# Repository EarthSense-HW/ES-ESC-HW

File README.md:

# ES-ESC-HW
Hardware source files for EarthSense ESC Based on VESC4

## Modifications from VESC4 Hardware:
* Changed form factor to fit onto EarthSense TerraSentia System Board
* Two IO Pins are broken out for auto-setting CAN ID based on placement on EarthSense TerraSentia System Board
* MOSFETs changed to flat 5x6 packages (STL260N)
* Changed various components in 5v regulator and 3.3v regulator circuits
* Removed IO pins that are not useful to EarthSense TerraSentia Robots
* SWD Programming header broken out to JST-ZH connector
* Two DIO broken out to JST-PH Connector for reading quadrature encoders

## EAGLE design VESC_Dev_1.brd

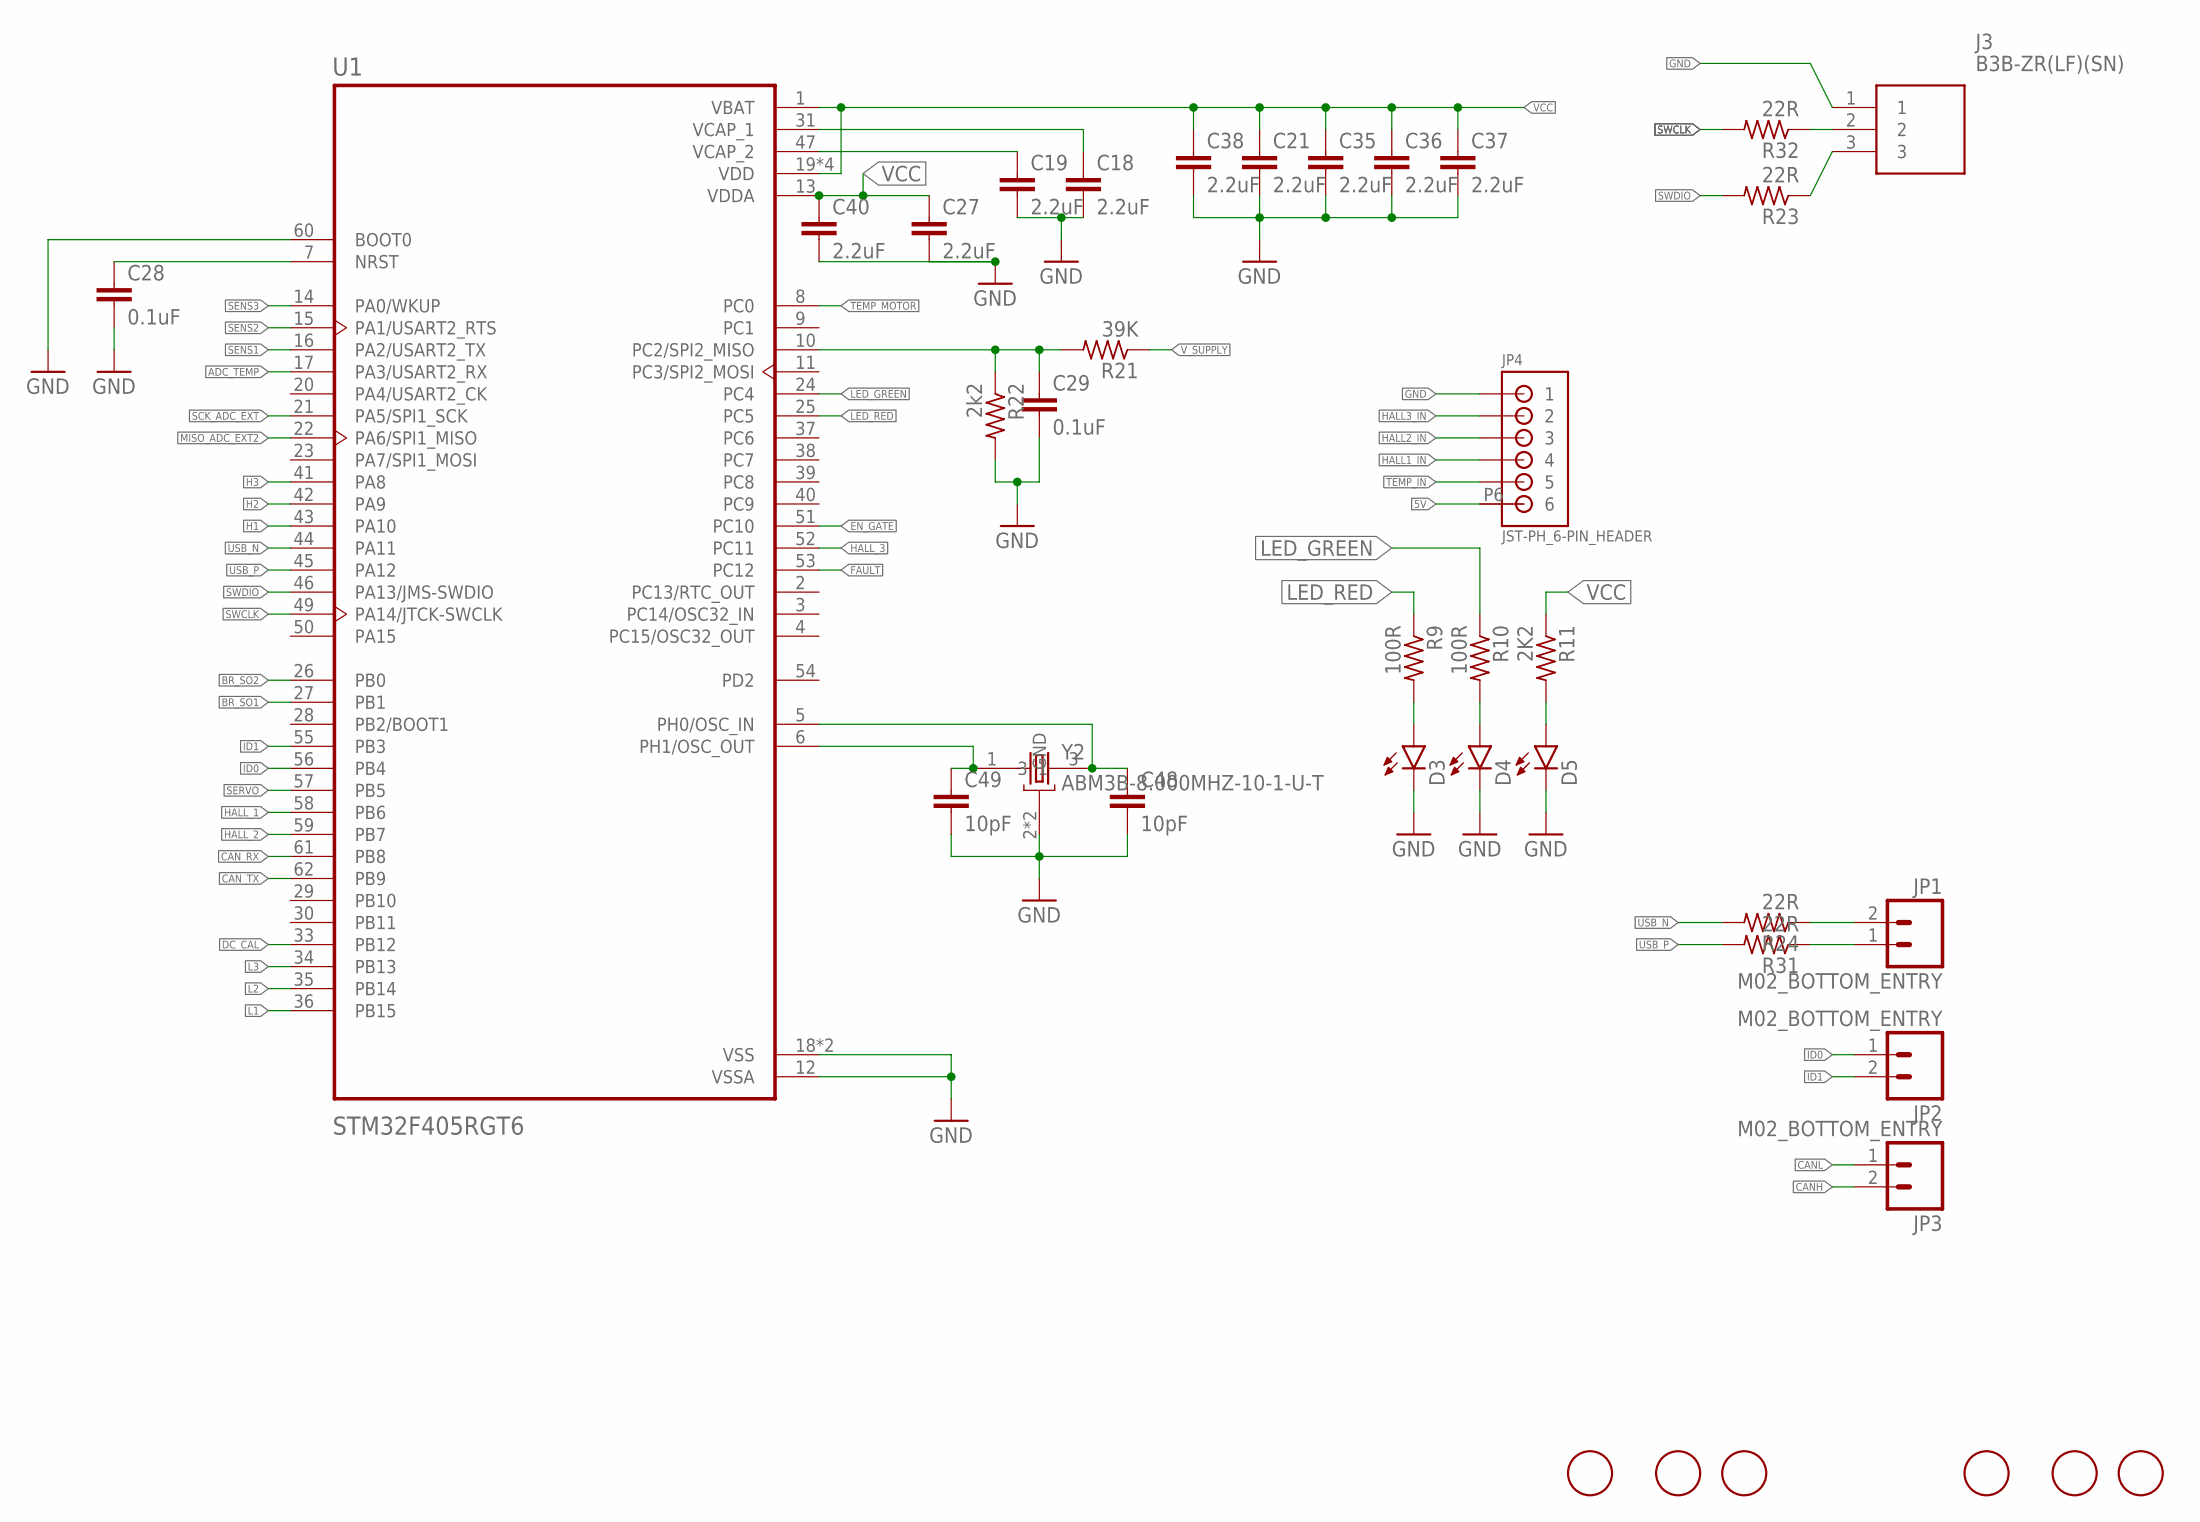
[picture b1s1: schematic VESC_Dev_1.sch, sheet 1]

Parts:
C18, C19, C21, C27, C35, C37, C38, C40: 2.2uF; C0603
C28, C29: 0.1uF; C0603
C36: 2.2uF; C0402
C48, C49: 10pF; C0603
D3, D4, D5: LEDSML0603; SML0603
J3: B3B-ZR(LF)(SN); SHDR3W50P0X150_1X3_600X350X450
JP1, JP2, JP3: M02_BOTTOM_ENTRY; 1X02_BOTTOM_ENTRY
JP4: JST-PH_6-PIN_HEADER; JST_B6B-PH_HEADER
R9, R10: 100R; R0603
R11: 2K2; R0603
R21: 39K; R0603
R22: 2k2; R0603
R23, R24, R31, R32: 22R; R0603
U1: STM32F405RGT6; QFP50P1200X1200X160-64N
U$1, U$2, U$3, U$4, U$5, U$6: FIDUCIAL; FIDUCIAL_1MM
Y2: ABM3B-8.000MHZ-10-1-U-T; OSCCC500X320X110-4N

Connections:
5V: JP4.P6 (6); also elsewhere on the board
ADC_TEMP: U1.17 (PA3/USART2_RX); also elsewhere on the board
BR_SO1: U1.27 (PB1); also elsewhere on the board
BR_SO2: U1.26 (PB0); also elsewhere on the board
CANH: JP3.2; also elsewhere on the board
CANL: JP3.1; also elsewhere on the board
CAN_RX: U1.61 (PB8); also elsewhere on the board
CAN_TX: U1.62 (PB9); also elsewhere on the board
DC_CAL: U1.33 (PB12); also elsewhere on the board
EN_GATE: U1.51 (PC10); also elsewhere on the board
FAULT: U1.53 (PC12); also elsewhere on the board
GND: C18.2, C19.2, C21.2, C27.2, C28.2, C29.2, C35.2, C36.2, C37.2, C38.2, C40.2, C48.2, C49.2, D3.C, D4.C, D5.C, J3.1, JP4.P1 (1), R22.2, U1.12 (VSSA), U1.18 (VSS), U1.60 (BOOT0), U1.63 (VSS), Y2.2 (GND), Y2.4 (GND); also elsewhere on the board
H1: U1.43 (PA10); also elsewhere on the board
H2: U1.42 (PA9); also elsewhere on the board
H3: U1.41 (PA8); also elsewhere on the board
HALL1_IN: JP4.P4 (4); also elsewhere on the board
HALL2_IN: JP4.P3 (3); also elsewhere on the board
HALL3_IN: JP4.P2 (2); also elsewhere on the board
HALL_1: U1.58 (PB6); also elsewhere on the board
HALL_2: U1.59 (PB7); also elsewhere on the board
HALL_3: U1.52 (PC11); also elsewhere on the board
ID0: JP2.1, U1.56 (PB4)
ID1: JP2.2, U1.55 (PB3)
L1: U1.36 (PB15); also elsewhere on the board
L2: U1.35 (PB14); also elsewhere on the board
L3: U1.34 (PB13); also elsewhere on the board
LED_GREEN: R10.1, U1.24 (PC4)
LED_RED: R9.1, U1.25 (PC5)
MISO_ADC_EXT2: U1.22 (PA6/SPI1_MISO)
unnamed: C28.1, U1.7 (NRST)
unnamed: J3.2, R32.1
unnamed: C29.1, R21.2, R22.1, U1.10 (PC2/SPI2_MISO)
unnamed: JP1.2, R24.1
unnamed: C18.1, U1.31 (VCAP_1)
unnamed: JP1.1, R31.1
unnamed: C19.1, U1.47 (VCAP_2)
unnamed: C49.1, U1.6 (PH1/OSC_OUT), Y2.1
unnamed: C48.1, U1.5 (PH0/OSC_IN), Y2.3
unnamed: J3.3, R23.1
unnamed: D3.A, R9.2
unnamed: D4.A, R10.2
unnamed: D5.A, R11.2
SCK_ADC_EXT: U1.21 (PA5/SPI1_SCK)
SENS1: U1.16 (PA2/USART2_TX); also elsewhere on the board
SENS2: U1.15 (PA1/USART2_RTS); also elsewhere on the board
SENS3: U1.14 (PA0/WKUP); also elsewhere on the board
SERVO: U1.57 (PB5)
SWCLK: R32.2, U1.49 (PA14/JTCK-SWCLK)
SWDIO: R23.2, U1.46 (PA13/JMS-SWDIO)
TEMP_IN: JP4.P5 (5)
TEMP_MOTOR: U1.8 (PC0); also elsewhere on the board
USB_N: R24.2, U1.44 (PA11)
USB_P: R31.2, U1.45 (PA12)
VCC: C21.1, C27.1, C35.1, C36.1, C37.1, C38.1, C40.1, R11.1, U1.1 (VBAT), U1.13 (VDDA), U1.19 (VDD), U1.32 (VDD), U1.48 (VDD), U1.64 (VDD); also elsewhere on the board
V_SUPPLY: R21.1; also elsewhere on the board

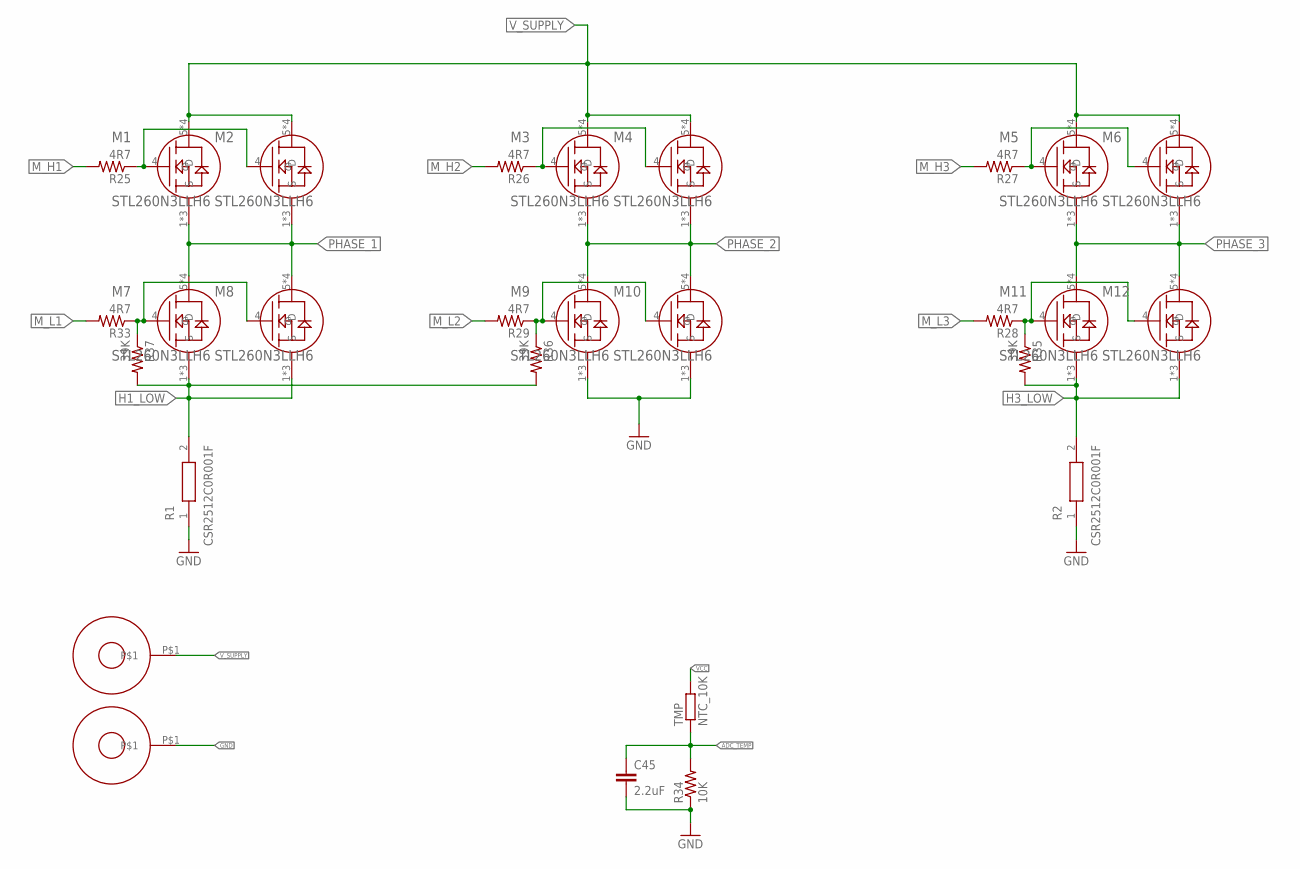
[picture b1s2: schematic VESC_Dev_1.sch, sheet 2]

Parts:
C45: 2.2uF; C0603
M1, M2, M3, M4, M5, M6, M7, M8, M9, M10, M11, M12: STL260N3LLH6; TRANS_STL60P4LLF6
R1, R2: CSR2512C0R001F; RESC6432X85N
R25, R26, R27, R28, R29, R33: 4R7; R0603
R34: 10K; R0603
R35, R36, R37: 39K; R0603
TMP: NTC_10K; R0402
U$7, U$8: M3_POWER_HOLE

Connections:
ADC_TEMP: C45.1, R34.2, TMP.1; also elsewhere on the board
GND: C45.2, M9.1 (S), M9.2 (S), M9.3 (S), M10.1 (S), M10.2 (S), M10.3 (S), R1.1, R2.1, R34.1, U$8.P$1; also elsewhere on the board
H1_LOW: M7.1 (S), M7.2 (S), M7.3 (S), M8.1 (S), M8.2 (S), M8.3 (S), R1.2, R36.2, R37.2; also elsewhere on the board
H3_LOW: M11.1 (S), M11.2 (S), M11.3 (S), M12.1 (S), M12.2 (S), M12.3 (S), R2.2, R35.2; also elsewhere on the board
M_H1: R25.2; also elsewhere on the board
M_H2: R26.2; also elsewhere on the board
M_H3: R27.2; also elsewhere on the board
M_L1: R33.2; also elsewhere on the board
M_L2: R29.2; also elsewhere on the board
M_L3: R28.2; also elsewhere on the board
unnamed: M1.4 (G), M2.4 (G), R25.1
unnamed: M11.4 (G), M12.4 (G), R28.1, R35.1
unnamed: M7.4 (G), M8.4 (G), R33.1, R37.1
unnamed: M3.4 (G), M4.4 (G), R26.1
unnamed: M9.4 (G), M10.4 (G), R29.1, R36.1
unnamed: M5.4 (G), M6.4 (G), R27.1
PHASE_1: M1.1 (S), M1.2 (S), M1.3 (S), M2.1 (S), M2.2 (S), M2.3 (S), M7.5 (D), M7.6 (D), M7.7 (D), M7.8 (D), M8.5 (D), M8.6 (D), M8.7 (D), M8.8 (D); also elsewhere on the board
PHASE_2: M3.1 (S), M3.2 (S), M3.3 (S), M4.1 (S), M4.2 (S), M4.3 (S), M9.5 (D), M9.6 (D), M9.7 (D), M9.8 (D), M10.5 (D), M10.6 (D), M10.7 (D), M10.8 (D); also elsewhere on the board
PHASE_3: M5.1 (S), M5.2 (S), M5.3 (S), M6.1 (S), M6.2 (S), M6.3 (S), M11.5 (D), M11.6 (D), M11.7 (D), M11.8 (D), M12.5 (D), M12.6 (D), M12.7 (D), M12.8 (D); also elsewhere on the board
VCC: TMP.2; also elsewhere on the board
V_SUPPLY: M1.5 (D), M1.6 (D), M1.7 (D), M1.8 (D), M2.5 (D), M2.6 (D), M2.7 (D), M2.8 (D), M3.5 (D), M3.6 (D), M3.7 (D), M3.8 (D), M4.5 (D), M4.6 (D), M4.7 (D), M4.8 (D), M5.5 (D), M5.6 (D), M5.7 (D), M5.8 (D), M6.5 (D), M6.6 (D), M6.7 (D), M6.8 (D), U$7.P$1; also elsewhere on the board

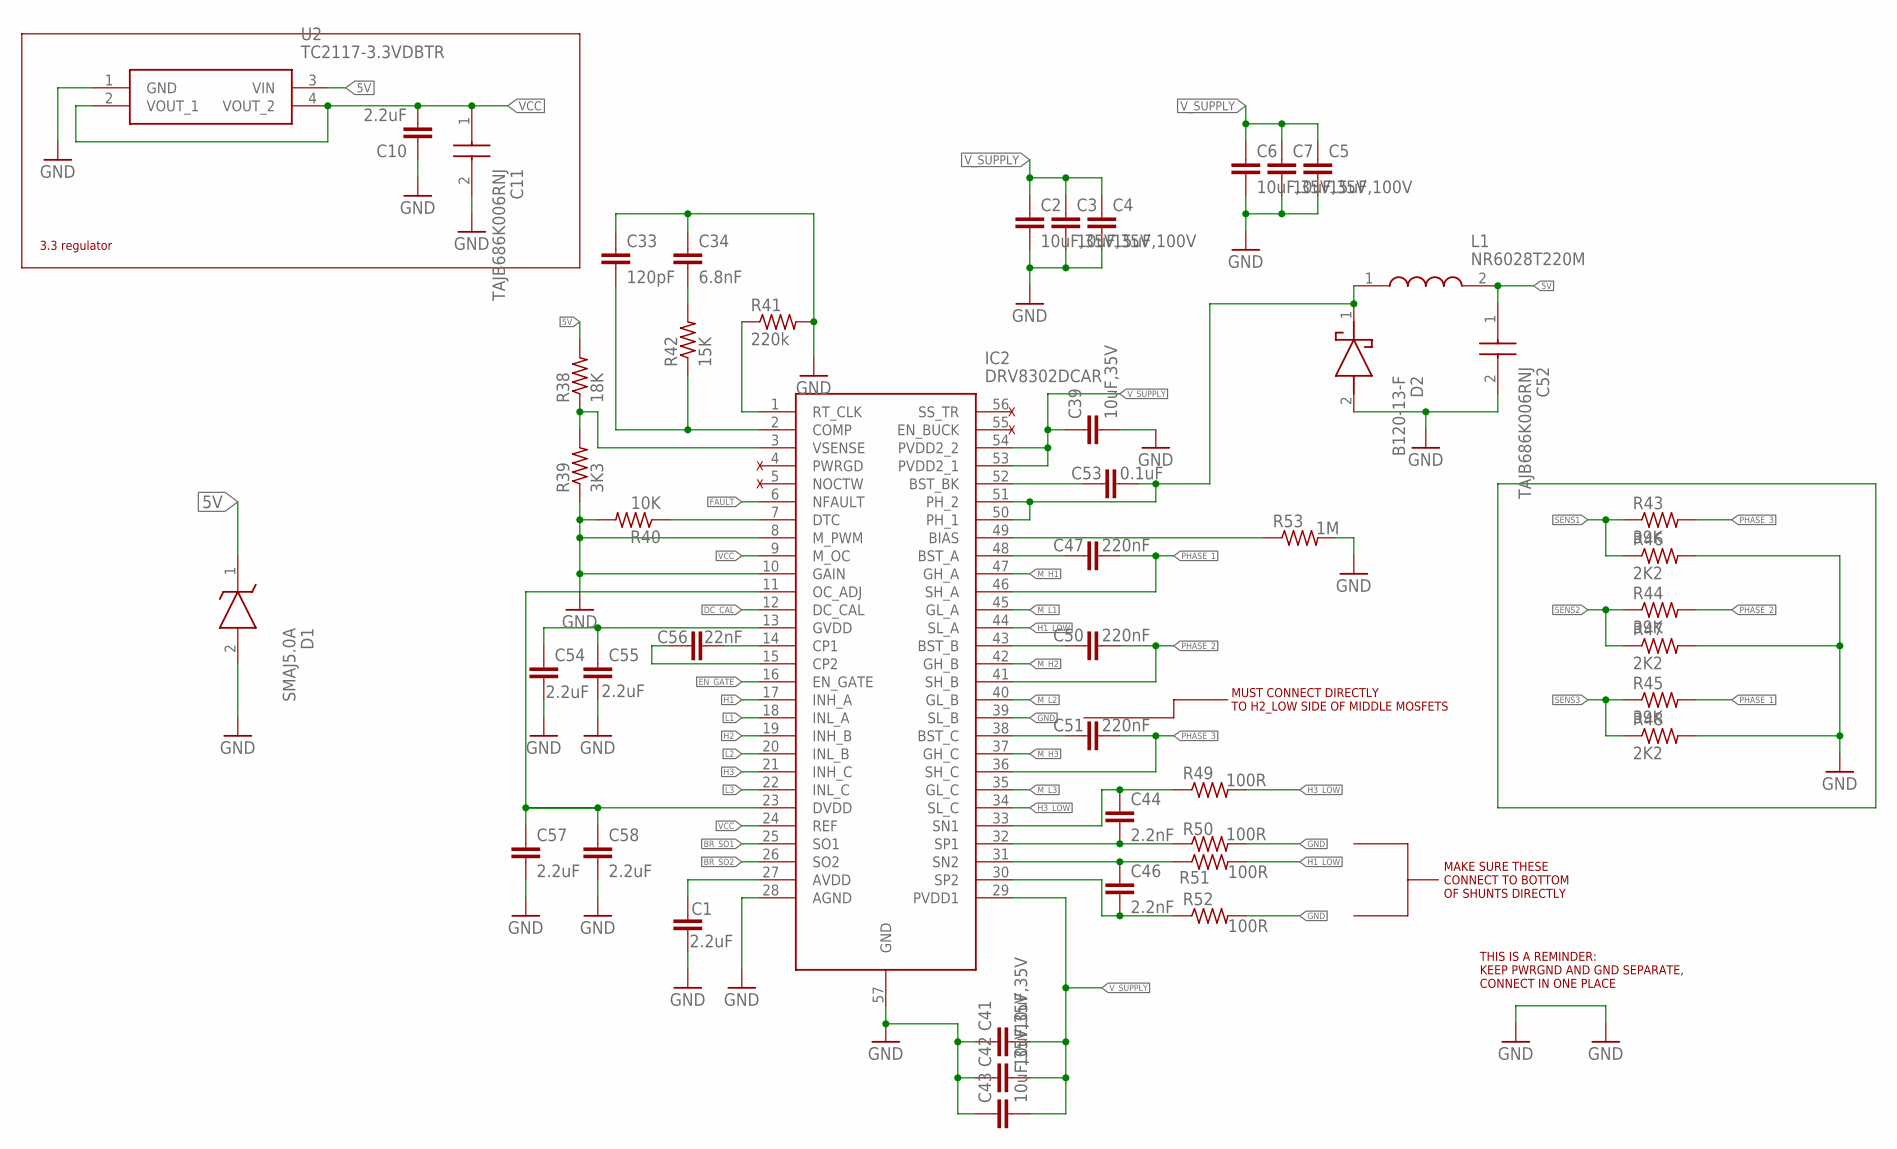
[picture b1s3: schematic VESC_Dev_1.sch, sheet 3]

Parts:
C1, C54, C55: 2.2uF; C0603
C2, C3, C6, C7, C39, C41, C42, C43: 10uF,35V; C0805
C4, C5: 15uF,100V; C2220K
C10: 2.2uF; C0805
C11, C52: TAJB686K006RNJ; CAPPM3528X210N
C33: 120pF; C0402
C34: 6.8nF; C0402
C44, C46: 2.2nF; C0402
C47, C50, C51: 220nF; C0402
C53: 0.1uF; C0603
C56: 22nF; C0402
C57, C58: 2.2uF; C0402
D1: SMAJ5.0A; DIOM5026X229N
D2: B120-13-F; DIOM5226X240N
IC2: DRV8302DCAR; SOP50P810X120-57N
L1: NR6028T220M
R38: 18K; R0402
R39: 3K3; R0402
R40: 10K; R0603
R41: 220k; R0402
R42: 15K; R0402
R43, R44, R45: 39K; R0603
R46, R47, R48: 2K2; R0603
R49, R50, R51, R52: 100R; R0402
R53: 1M; R0603
U2: TC2117-3.3VDBTR; SOT230P700X180-4N

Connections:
5V: C52.1 (+), D1.1 (K), L1.2, R38.2, U2.3 (VIN); also elsewhere on the board
BR_SO1: IC2.25 (SO1); also elsewhere on the board
BR_SO2: IC2.26 (SO2); also elsewhere on the board
DC_CAL: IC2.12 (DC_CAL); also elsewhere on the board
EN_GATE: IC2.16 (EN_GATE); also elsewhere on the board
FAULT: IC2.6 (NFAULT); also elsewhere on the board
GND: C1.2, C2.2, C3.2, C4.2, C5.2, C6.2, C7.2, C10.1, C11.2 (-), C33.1, C34.1, C39.2, C41.1, C42.1, C43.1, C52.2 (-), C54.2, C55.2, C57.2, C58.2, D1.2 (A), D2.2 (A), IC2.8 (M_PWM), IC2.10 (GAIN), IC2.28 (AGND), IC2.39 (SL_B), IC2.57 (GND), R39.1, R40.2, R41.2, R46.2, R47.2, R48.2, R50.2, R52.2, R53.2, U2.1 (GND); also elsewhere on the board
H1: IC2.17 (INH_A); also elsewhere on the board
H1_LOW: IC2.44 (SL_A), R51.2; also elsewhere on the board
H2: IC2.19 (INH_B); also elsewhere on the board
H3: IC2.21 (INH_C); also elsewhere on the board
H3_LOW: IC2.34 (SL_C), R49.2; also elsewhere on the board
L1: IC2.18 (INL_A); also elsewhere on the board
L2: IC2.20 (INL_B); also elsewhere on the board
L3: IC2.22 (INL_C); also elsewhere on the board
M_H1: IC2.47 (GH_A); also elsewhere on the board
M_H2: IC2.42 (GH_B); also elsewhere on the board
M_H3: IC2.37 (GH_C); also elsewhere on the board
M_L1: IC2.45 (GL_A); also elsewhere on the board
M_L2: IC2.40 (GL_B); also elsewhere on the board
M_L3: IC2.35 (GL_C); also elsewhere on the board
unnamed: C57.1, C58.1, IC2.11 (OC_ADJ), IC2.23 (DVDD)
unnamed: IC2.3 (VSENSE), R38.1, R39.2
unnamed: IC2.7 (DTC), R40.1
unnamed: C54.1, C55.1, IC2.13 (GVDD)
unnamed: C56.2, IC2.14 (CP1)
unnamed: C56.1, IC2.15 (CP2)
unnamed: IC2.1 (RT_CLK), R41.1
unnamed: C33.2, IC2.2 (COMP), R42.1
unnamed: C34.2, R42.2
unnamed: C1.1, IC2.27 (AVDD)
unnamed: IC2.49 (BIAS), R53.1
unnamed: C46.2, IC2.30 (SP2), R52.1
unnamed: C46.1, IC2.31 (SN2), R51.1
unnamed: C44.1, IC2.33 (SN1), R49.1
unnamed: C44.2, IC2.32 (SP1), R50.1
unnamed: C51.1, IC2.38 (BST_C)
unnamed: C50.1, IC2.43 (BST_B)
unnamed: C47.1, IC2.48 (BST_A)
unnamed: C53.1, IC2.52 (BST_BK)
unnamed: C53.2, D2.1 (K), IC2.50 (PH_1), IC2.51 (PH_2), L1.1
PHASE_1: C47.2, IC2.46 (SH_A), R45.2; also elsewhere on the board
PHASE_2: C50.2, IC2.41 (SH_B), R44.2; also elsewhere on the board
PHASE_3: C51.2, IC2.36 (SH_C), R43.2; also elsewhere on the board
SENS1: R43.1, R46.1; also elsewhere on the board
SENS2: R44.1, R47.1; also elsewhere on the board
SENS3: R45.1, R48.1; also elsewhere on the board
VCC: C10.2, C11.1 (+), IC2.9 (M_OC), IC2.24 (REF), U2.2 (VOUT_1), U2.4 (VOUT_2); also elsewhere on the board
V_SUPPLY: C2.1, C3.1, C4.1, C5.1, C6.1, C7.1, C39.1, C41.2, C42.2, C43.2, IC2.29 (PVDD1), IC2.53 (PVDD2_1), IC2.54 (PVDD2_2); also elsewhere on the board

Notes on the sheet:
3.3 regulator
MAKE SURE THESE CONNECT TO BOTTOM OF SHUNTS DIRECTLY
THIS IS A REMINDER: KEEP PWRGND AND GND SEPARATE, CONNECT IN ONE PLACE
MUST CONNECT DIRECTLY TO H2_LOW SIDE OF MIDDLE MOSFETS

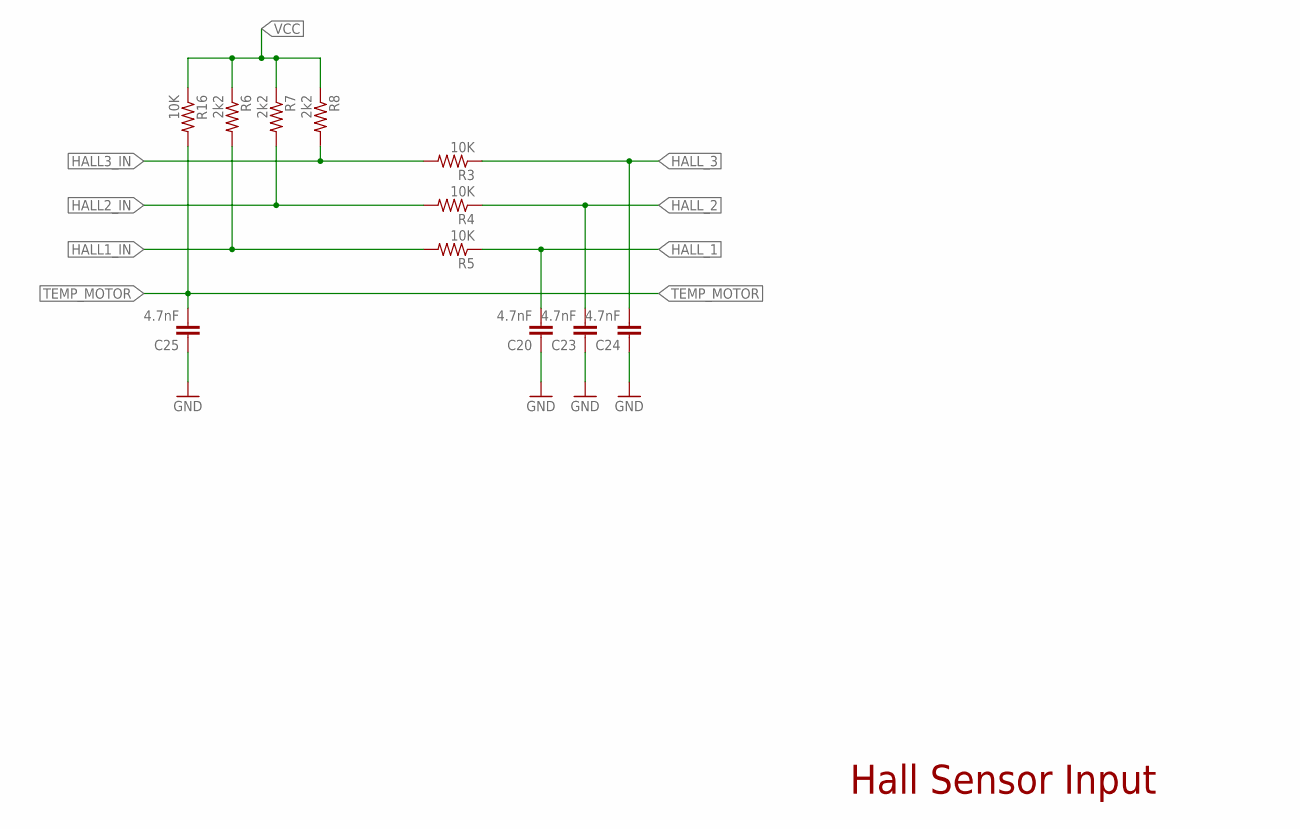
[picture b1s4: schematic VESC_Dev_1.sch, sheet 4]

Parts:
C20, C23, C24, C25: 4.7nF; C0603
R3, R4, R5, R16: 10K; R0603
R6, R7, R8: 2k2; R0603

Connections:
GND: C20.1, C23.1, C24.1, C25.1; also elsewhere on the board
HALL1_IN: R5.2, R6.2; also elsewhere on the board
HALL2_IN: R4.2, R7.2; also elsewhere on the board
HALL3_IN: R3.2, R8.2; also elsewhere on the board
HALL_1: C20.2, R5.1; also elsewhere on the board
HALL_2: C23.2, R4.1; also elsewhere on the board
HALL_3: C24.2, R3.1; also elsewhere on the board
TEMP_MOTOR: C25.2, R16.2; also elsewhere on the board
VCC: R6.1, R7.1, R8.1, R16.1; also elsewhere on the board

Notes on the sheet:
Hall Sensor Input

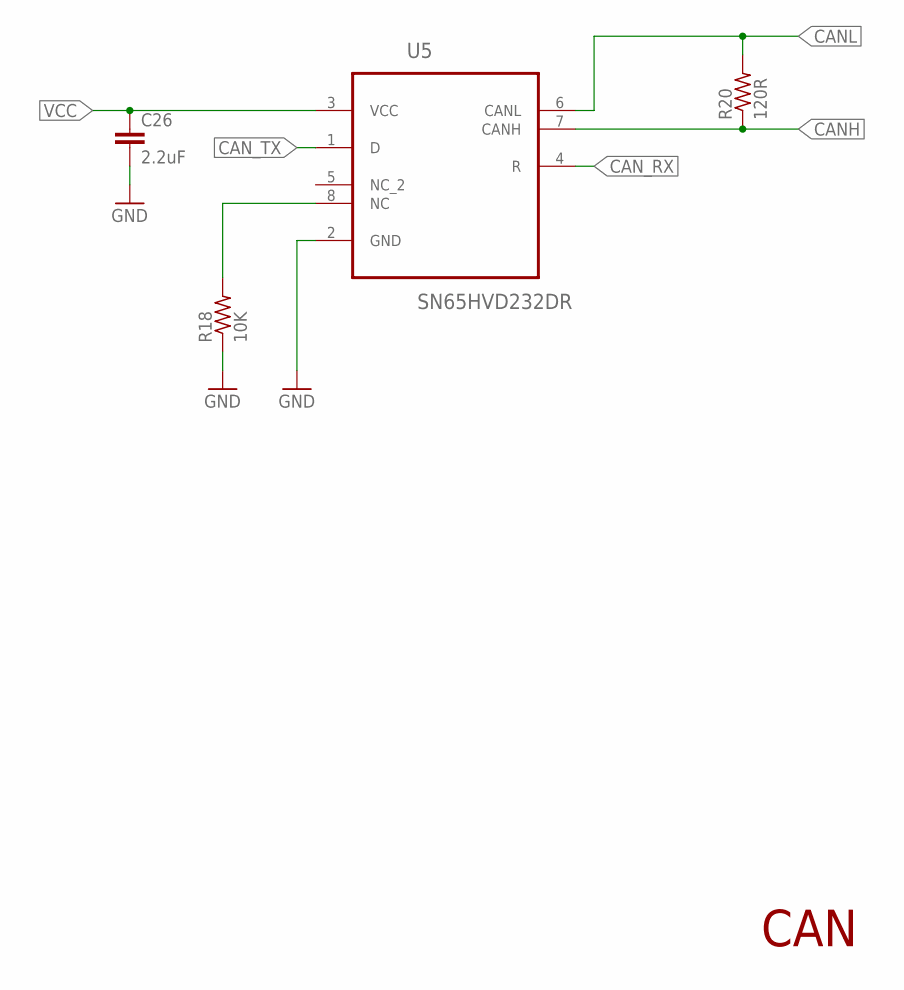
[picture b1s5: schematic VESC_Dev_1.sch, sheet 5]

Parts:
C26: 2.2uF; C0603
R18: 10K; R0603
R20: 120R; R0603
U5: SN65HVD232DR; SOIC127P600X175-8N

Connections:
CANH: R20.1, U5.7 (CANH); also elsewhere on the board
CANL: R20.2, U5.6 (CANL); also elsewhere on the board
CAN_RX: U5.4 (R); also elsewhere on the board
CAN_TX: U5.1 (D); also elsewhere on the board
GND: C26.2, R18.1, U5.2 (GND); also elsewhere on the board
unnamed: R18.2, U5.8 (NC)
VCC: C26.1, U5.3 (VCC); also elsewhere on the board

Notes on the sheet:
CAN

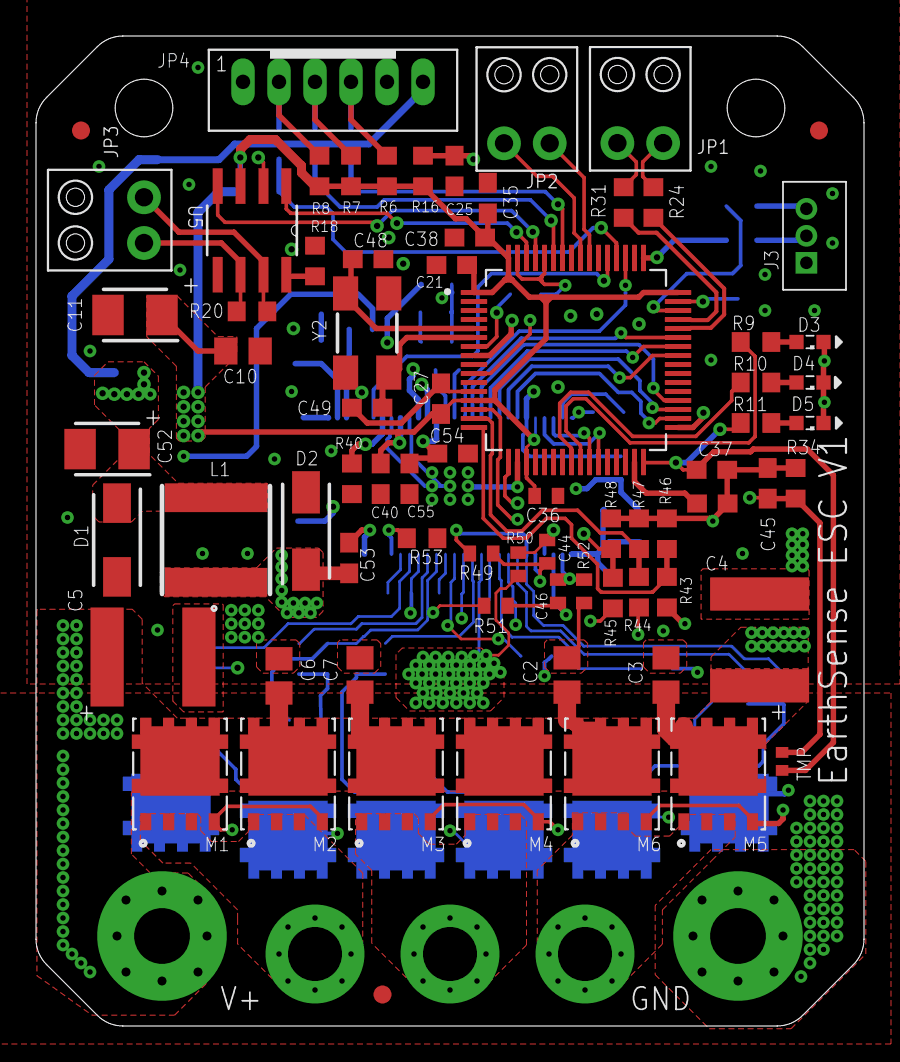
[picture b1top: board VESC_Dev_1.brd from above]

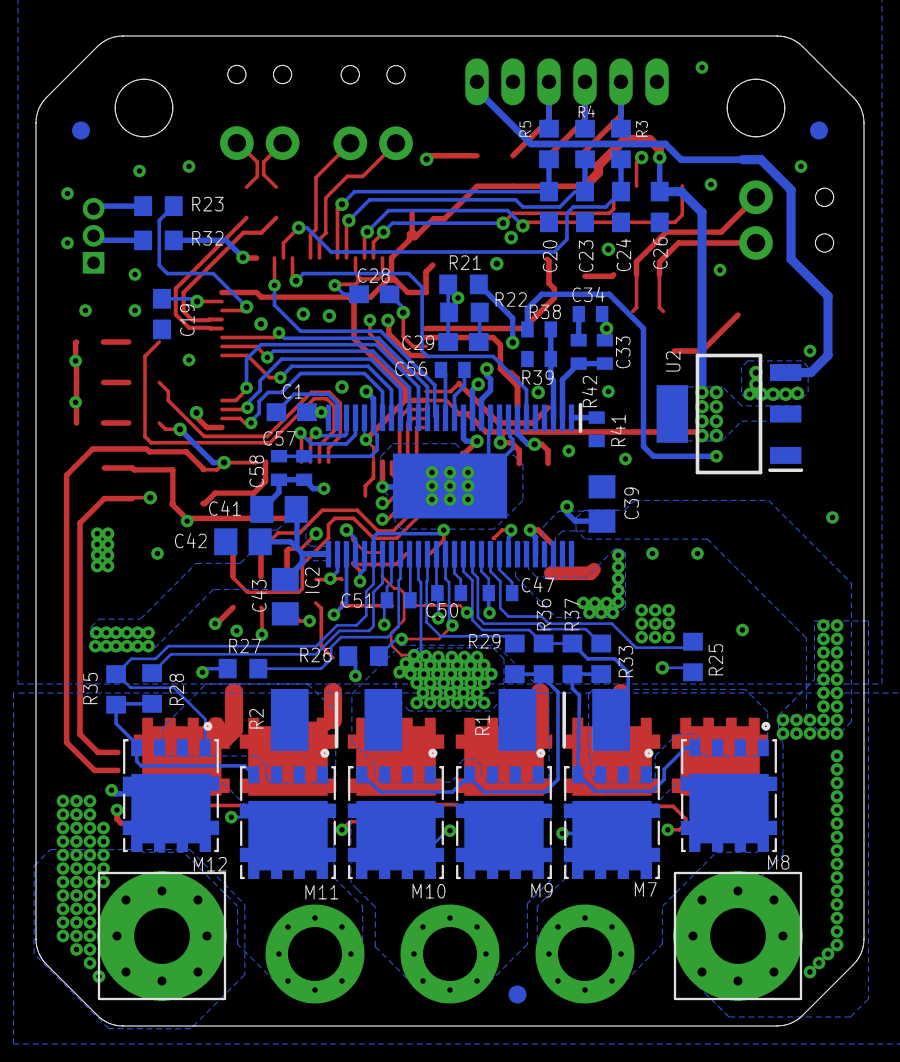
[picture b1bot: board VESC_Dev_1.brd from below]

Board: 4 copper layers, 46.0 x 55.0 mm, 129 parts (53 on the bottom side), 89 nets.

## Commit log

2020-06-20 Added ESC Hardware Files

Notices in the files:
parts and their libraries:
SparkFun-Connectors: Licensing: CC v3.0 Share-Alike You are welcome to use this library for commercial purposes.
